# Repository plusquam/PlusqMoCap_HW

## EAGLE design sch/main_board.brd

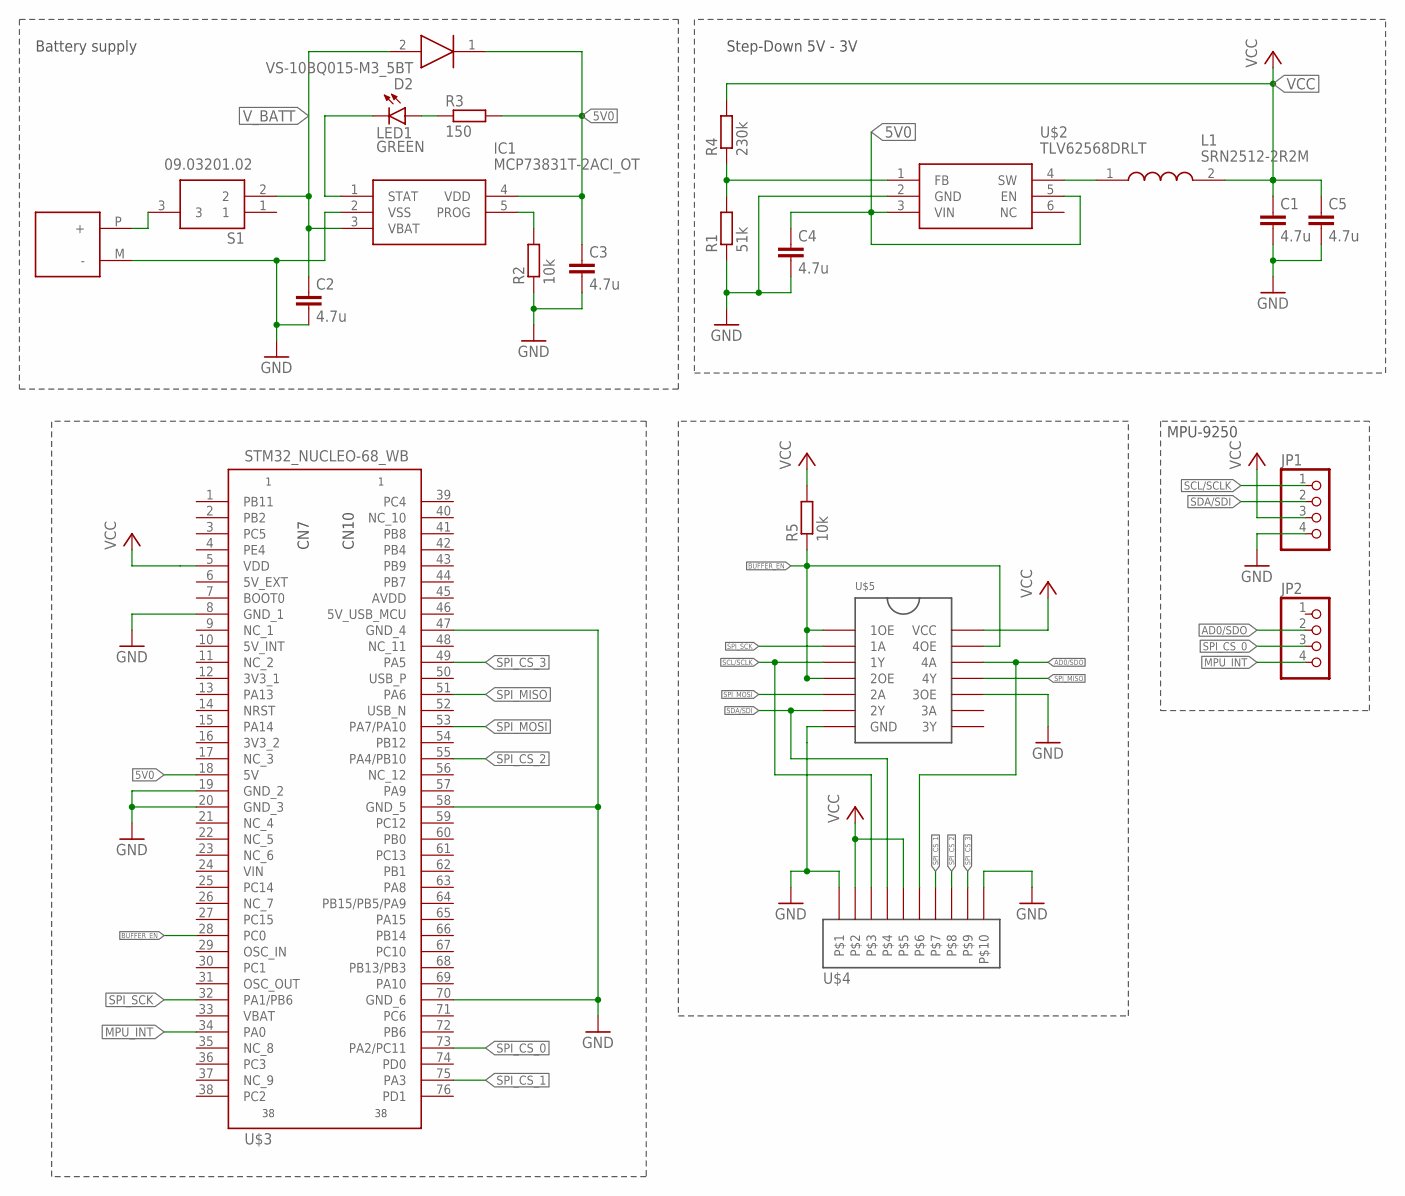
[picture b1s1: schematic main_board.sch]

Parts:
C1, C2, C3, C4, C5: 4.7u; C1206
D2: VS-10BQ015-M3_5BT; DIOM5436X244N
IC1: MCP73831T-2ACI_OT; SOT95P270X145-5N
JP1, JP2: PINHD-1X04_2.54-SMD; 1X04SMD
L1: SRN2512-2R2M; INDPM2622X120N
LED1: GREEN; CHIPLED_1206
R1: 51k; R1206
R2, R5: 10k; R1206
R3: 150; R1206
R4: 230k; R1206
S1: 09.03201.02; 090320102
U$1: BAT_FLAT_PAD; BATTERY_FLAT_PAD
U$2: TLV62568DRLT; SOT563
U$3: STM32_NUCLEO-68_WB; STM32_NUCLEO-68_FOOTPRINT
U$4: 1-2178711-2; 1-2178712-0
U$5: 74AHC126D,118; SOIC127P600X175-14N

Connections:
5V0: C3.1, C4.1, D2.1 (K), IC1.4 (VDD), R3.2, U$2.3 (VIN), U$2.5 (EN), U$3.18 (5V)
AD0/SDO: JP2.2, U$4.P$6, U$5.12 (4A)
BUFFER_EN: R5.1, U$3.28 (PC0), U$5.1 (1OE), U$5.4 (2OE), U$5.13 (4OE)
GND: C1.2, C2.2, C3.2, C4.2, C5.2, IC1.2 (VSS), JP1.4, R1.1, R2.1, U$1.M (-), U$2.2 (GND), U$3.8 (GND_1), U$3.19 (GND_2), U$3.20 (GND_3), U$3.47 (GND_4), U$3.58 (GND_5), U$3.70 (GND_6), U$4.P$1, U$4.P$10, U$5.7 (GND), U$5.10 (3OE)
MPU_INT: JP2.4, U$3.34 (PA0)
unnamed: LED1.A, R3.1
unnamed: IC1.1 (STAT), LED1.C
unnamed: IC1.5 (PROG), R2.2
unnamed: S1.3, U$1.P (+)
unnamed: L1.1, U$2.4 (SW)
unnamed: R1.2, R4.1, U$2.1 (FB)
SCL/SCLK: JP1.1, U$4.P$3, U$5.3 (1Y)
SDA/SDI: JP1.2, U$4.P$4, U$5.6 (2Y)
SPI_CS_0: JP2.3, U$3.73 (PA2/PC11)
SPI_CS_1: U$3.75 (PA3), U$4.P$7
SPI_CS_2: U$3.55 (PA4/PB10), U$4.P$8
SPI_CS_3: U$3.49 (PA5), U$4.P$9
SPI_MISO: U$3.51 (PA6), U$5.11 (4Y)
SPI_MOSI: U$3.53 (PA7/PA10), U$5.5 (2A)
SPI_SCK: U$3.32 (PA1/PB6), U$5.2 (1A)
VCC: C1.1, C5.1, JP1.3, L1.2, R4.2, R5.2, U$3.5 (VDD), U$4.P$2, U$4.P$5, U$5.14 (VCC)
V_BATT: C2.1, D2.2 (A), IC1.3 (VBAT), S1.2

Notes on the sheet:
Step-Down 5V - 3V
Battery supply
MPU-9250

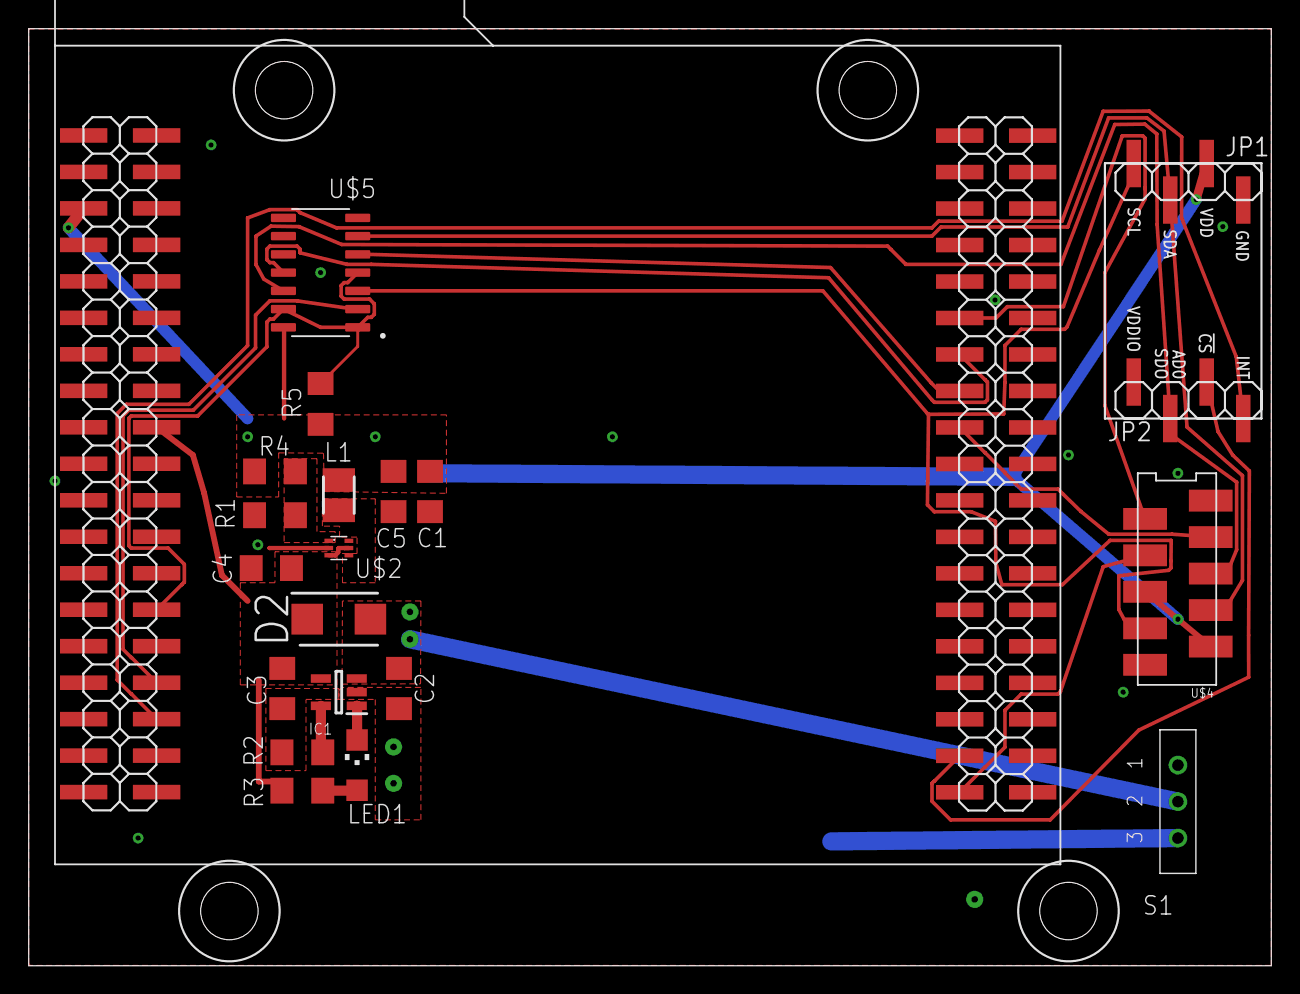
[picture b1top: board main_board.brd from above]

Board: 2 copper layers, 86.5 x 65.2 mm, 22 parts (1 on the bottom side), 22 nets.

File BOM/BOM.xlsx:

|  |  | Main Board BOM
Item # | *Ref Des | *Qty | Manufacturer | *Mfg Part # | Description / Value | *Package | Type | Your Instructions / Notes
1 | C1,C2,C3,C4,C5 | 5 | VISHAY | VJ1206V475MXQTW1BC | Ceramic Capacitor, 4.7 µF, Y5V, 10 V | C1206 | SMD | (any/open) Any cheapest and available part which match specification.
2 | D2 | 1 | Vishay | VS-10BQ015-M3/5BT | VS-10BQ015-M3/5BT Vishay SMT Schottky Diode, 15V 1A, 2-Pin DO-214AA (SMB) | DO-214AA | SMD
3 | IC1 | 1 | Microchip | MCP73831T-2ACI/OT | Li-Ion Charge Controller 4.2V SOT23-5 | SOT-23 | SMD
4 | JP1,JP2 | 2 | MULTICOMP | 2212SM-04G-75-B1-PCR | Female pin header (socket), 1x4 slots, pitch 2,54mm | 1X04SMD | SMD | Given device is only example device, it can be replaced with any cheaper and av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
5 | L1 | 1 | Bourns | SRN2512-2R2M | Bourns SRN2512 Series Shielded Wire-wound SMD Inductor with a Ferrite Core, 2.2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 | INDPM2622X120N | SMD | Given device is only example device, it can be replaced with any cheaper and av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
6 | LED1 | 1 | KINGBRIGHT | KPT-3216SGC | Green LED in 1206 package, If = 20mA, Vf = 2,2V | 1206 | SMD | Given device is only example device, it can be replaced with any cheaper and av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
7 | R1 | 1 |  |  | 100kOhm, Thick Film Chip Resistor, 1% tolerance, Max. Dissipation 250mW | R1206 | SMD | (any/open) Any cheapest and available part which match specification.
8 | R2,R5 | 2 |  |  | 10kOhm, Thick Film Chip Resistor, 1% tolerance, Max. Dissipation 250mW | R1206 | SMD | (any/open) Any cheapest and available part which match specification.
9 | R3 | 1 |  |  | 150Ohm, Thick Film Chip Resistor, 1% tolerance, Max. Dissipation 250mW | R1206 | SMD | (any/open) Any cheapest and available part which match specification.
10 | R4 | 1 |  |  | 402kOhm, Thick Film Chip Resistor, 1% tolerance, Max. Dissipation 250mW | R1206 | SMD | (any/open) Any cheapest and available part which match specification.
11 | S1 | 1 | EOZ | 09.03201.02 | 2 Way Through Hole SIP Switch SPST, 500mA, 12Vdc | 3POS | thru-hole | Given device is only example device, it can be replaced with any cheaper and av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
12 | U$2 | 1 | TEXAS INSTRUMENTS | TLV62568DRLT | DC-DC buck converter | SOT563 | SMD
13 | U$4 | 1 | AMP - TE CONNECTIVITY | 1-2178711-0 | Headers & Wire Housings FOB, SMD, 10P, Pitch: 1,27mm | 2x5POS | SMD | Given device is only example device, it can be replaced with any cheaper and av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
14 | U$5 | 1 | NEXPERIA | 74AHC126D,118 | Buffers & Line Drivers QUAD 3-STATE BUS BUF | SOIC-14 | SMD | Given device is only example device, it can be replaced with any cheaper and av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
15 | CN7,CN10 | 2 |  |  | Female pin header (socket), 2x19 (38) slots, pitch 2,54mm | 2X19SMD | SMD | (any/open) Any cheapest and available part which match specification.
 |  |  | Sensor Board BOM
Item # | *Ref Des | *Qty | Manufacturer | *Mfg Part # | Description / Value | *Package | Type | Your Instructions / Notes
1 | JP1,JP2 | 2 | MULTICOMP | 2212SM-04G-75-B1-PCR | Female pin header (socket), 1x4 slots, pitch 2,54mm | 1X04SMD | SMD | Given device is only example device, it can be replaced with any cheaper and av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
2 | U$1 | 1 | NEXPERIA | 74AHC126D,118 | Buffers & Line Drivers QUAD 3-STATE BUS BUF | SOIC-14 | SMD | Given device is only example device, it can be replaced with any cheaper and av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
3 | U$2 | 1 | AMP - TE CONNECTIVITY | 1-2178711-0 | Headers & Wire Housings FOB, SMD, 10P, Pitch: 1,27mm | 2x5POS | SMD | Given device is only example device, it can be replaced with any cheaper and av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

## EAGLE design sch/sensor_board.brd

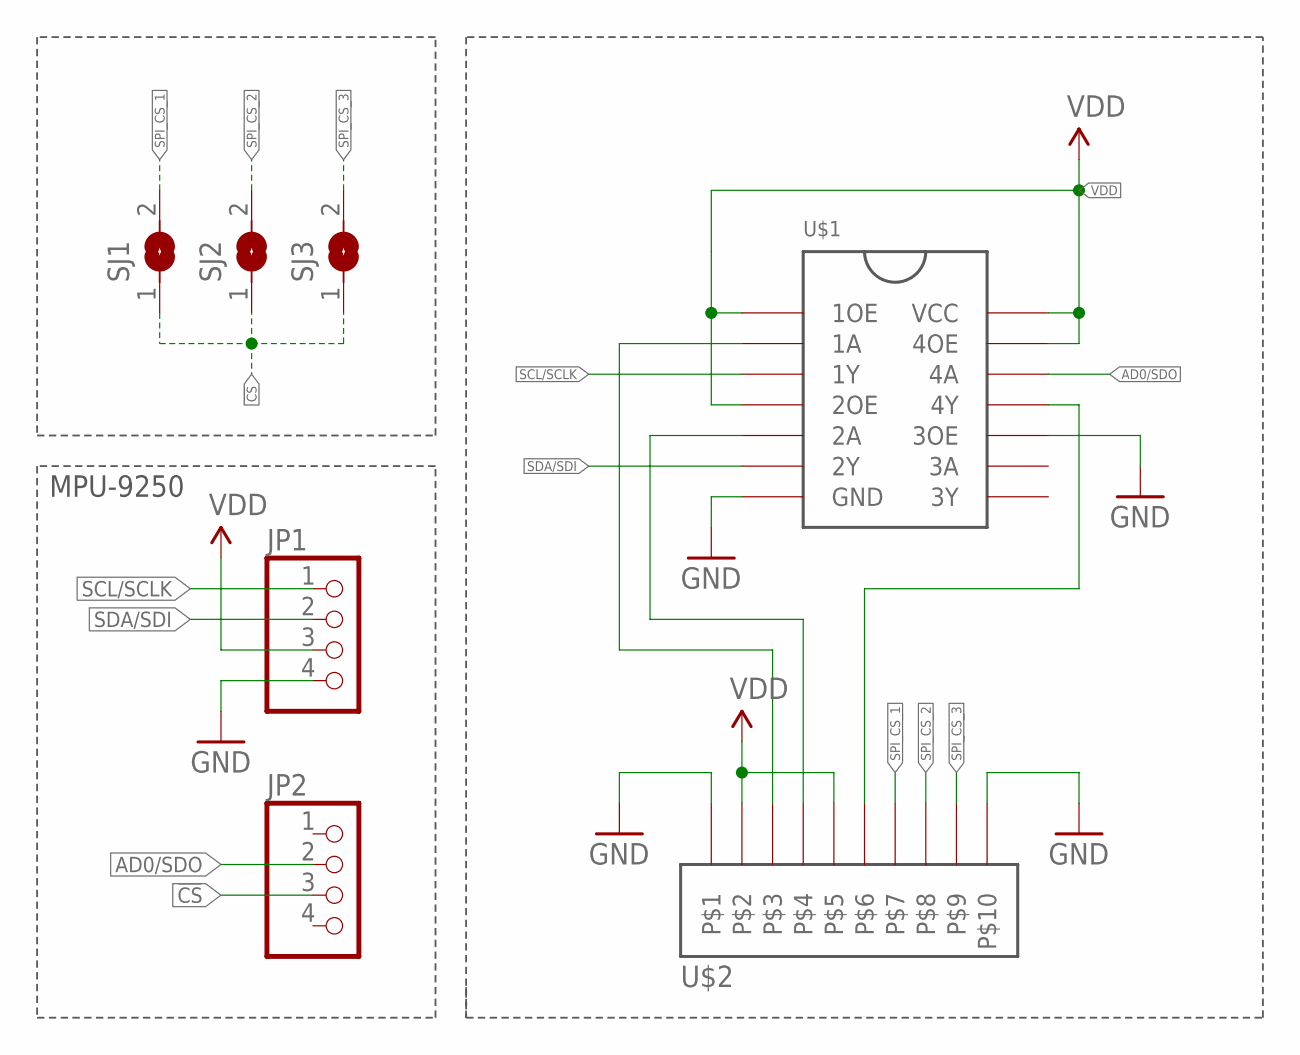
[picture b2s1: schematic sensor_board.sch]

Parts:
JP1, JP2: PINHD-1X04_2.54-SMD; 1X04SMD
SJ1, SJ2, SJ3: SJ
U$1: 74AHC126D,118; SOIC127P600X175-14N
U$2: 1-2178711-2; 1-2178712-0

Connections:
!CS: JP2.3, SJ1.1, SJ2.1, SJ3.1
AD0/SDO: JP2.2, U$1.12 (4A)
GND: JP1.4, U$1.7 (GND), U$1.10 (3OE), U$2.P$1, U$2.P$10
unnamed: U$1.2 (1A), U$2.P$3
unnamed: U$1.11 (4Y), U$2.P$6
unnamed: U$1.5 (2A), U$2.P$4
SCL/SCLK: JP1.1, U$1.3 (1Y)
SDA/SDI: JP1.2, U$1.6 (2Y)
SPI_CS_1: SJ1.2, U$2.P$7
SPI_CS_2: SJ2.2, U$2.P$8
SPI_CS_3: SJ3.2, U$2.P$9
VDD: JP1.3, U$1.1 (1OE), U$1.4 (2OE), U$1.13 (4OE), U$1.14 (VCC), U$2.P$2, U$2.P$5

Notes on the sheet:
MPU-9250

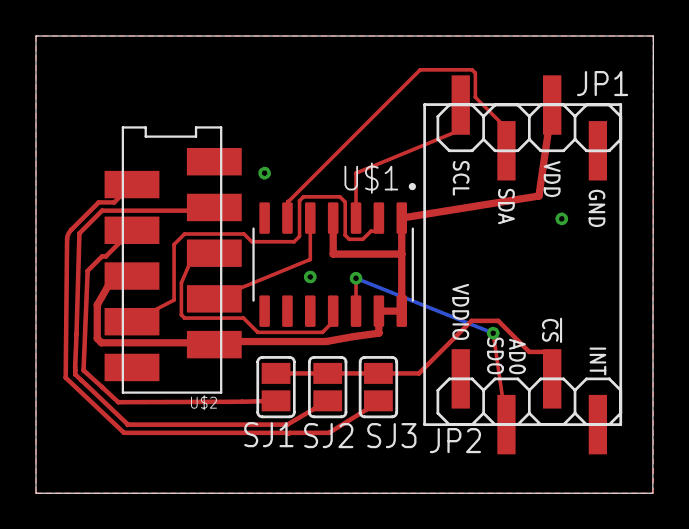
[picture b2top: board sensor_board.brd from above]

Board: 2 copper layers, 34.3 x 25.4 mm, 7 parts (0 on the bottom side), 12 nets.

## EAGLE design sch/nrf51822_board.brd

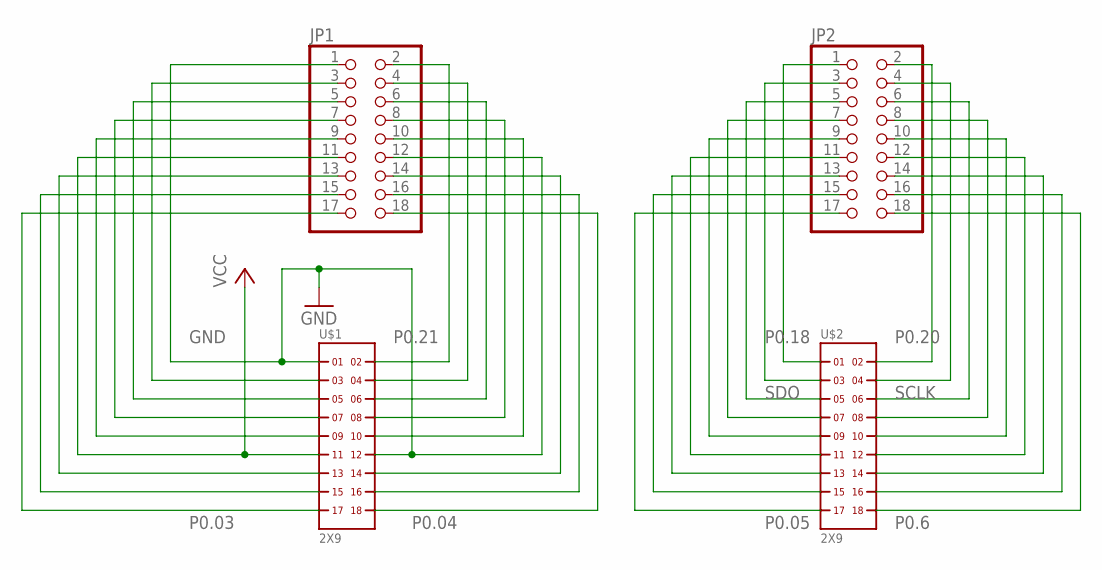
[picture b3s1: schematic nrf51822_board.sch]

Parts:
JP1, JP2: PINHD-2X9; 2X09
U$1, U$2: 2X9

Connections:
GND: JP1.1, JP1.12, U$1.1, U$1.12
unnamed: JP1.3, U$1.3
unnamed: JP1.5, U$1.5
unnamed: JP1.7, U$1.7
unnamed: JP1.9, U$1.9
unnamed: JP1.13, U$1.13
unnamed: JP1.15, U$1.15
unnamed: JP1.4, U$1.4
unnamed: JP1.6, U$1.6
unnamed: JP1.8, U$1.8
unnamed: JP1.10, U$1.10
unnamed: JP1.14, U$1.14
unnamed: JP1.16, U$1.16
unnamed: JP2.3, U$2.3
unnamed: JP2.7, U$2.7
unnamed: JP2.9, U$2.9
unnamed: JP2.11, U$2.11
unnamed: JP2.13, U$2.13
unnamed: JP2.15, U$2.15
unnamed: JP2.4, U$2.4
unnamed: JP2.8, U$2.8
unnamed: JP2.10, U$2.10
unnamed: JP2.12, U$2.12
unnamed: JP2.14, U$2.14
unnamed: JP2.16, U$2.16
P0.03: JP1.17, U$1.17
P0.04: JP1.18, U$1.18
P0.05: JP2.17, U$2.17
P0.6: JP2.18, U$2.18
P0.18: JP2.1, U$2.1
P0.20: JP2.2, U$2.2
P0.21: JP1.2, U$1.2
SCLK: JP2.6, U$2.6
SDO: JP2.5, U$2.5
VCC: JP1.11, U$1.11

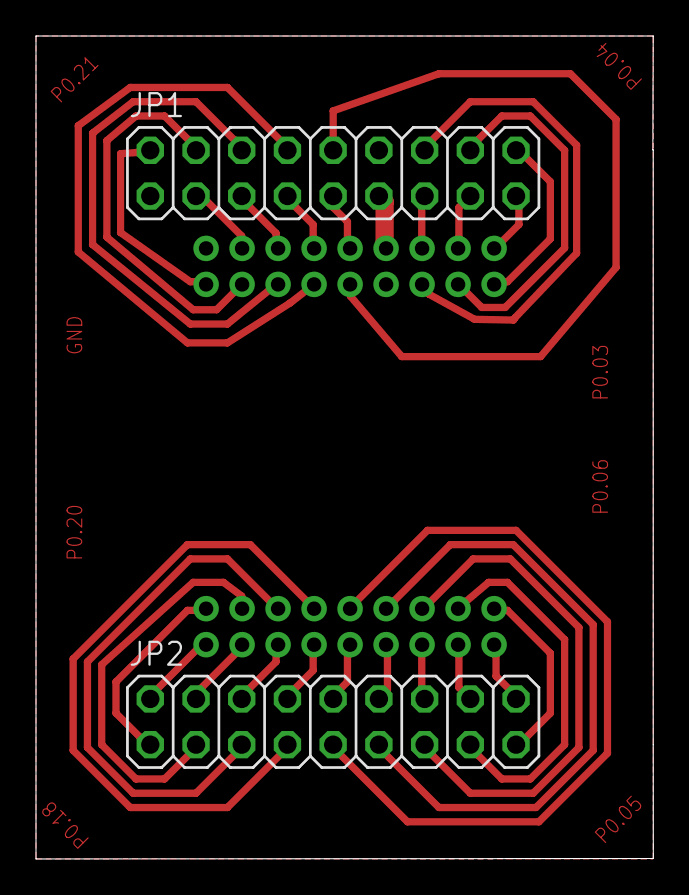
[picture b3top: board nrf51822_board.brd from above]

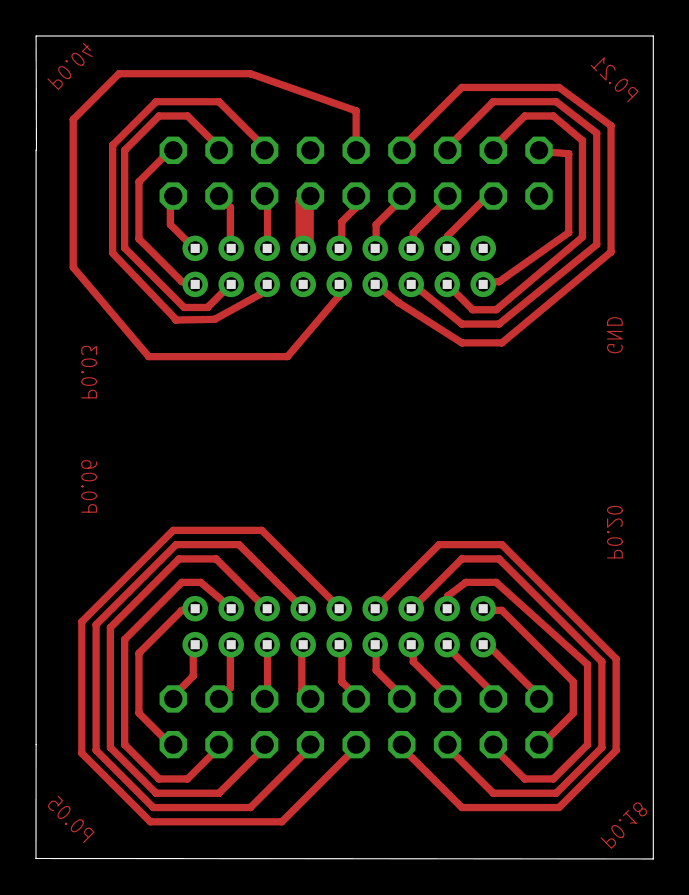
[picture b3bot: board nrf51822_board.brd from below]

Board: 2 copper layers, 34.3 x 45.7 mm, 4 parts (2 on the bottom side), 35 nets.

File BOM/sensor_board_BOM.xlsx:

|  |  | Sensor Board BOM
Item # | *Ref Des | *Qty | Manufacturer | *Mfg Part # | Description / Value | *Package | Type | Your Instructions / Notes
1 | JP1,JP2 | 2 | MULTICOMP | 2212SM-04G-75-B1-PCR | Female pin header (socket), 1x4 slots, pitch 2,54mm | 1X04SMD | SMD | Given device is only example device, it can be replaced with any cheaper and av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
2 | U$1 | 1 | NEXPERIA | 74AHC126D,118 | Buffers & Line Drivers QUAD 3-STATE BUS BUF | SOIC-14 | SMD | Given device is only example device, it can be replaced with any cheaper and av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
3 | U$2 | 1 | AMP - TE CONNECTIVITY | 1-2178711-0 | Headers & Wire Housings FOB, SMD, 10P, Pitch: 1,27mm | 2x5POS | SMD | Given device is only example device, it can be replaced with any cheaper and av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

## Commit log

2019-05-17 Import source files from PlusqMoCap repo.
2019-07-07 Remove obsolete license file.
2019-07-08 Add docs for STM32WB, Remove unused power supply elements.
2019-07-09 Add library for STM32WB prototype board.
2019-07-09 Create LICENSE
2019-08-14 Add STM32WB board part, add sensor connector part
2019-08-16 Main board ver. 1.0
2019-08-21 Ready for production HW version
2019-09-13 Add BOM files
2019-09-13 Change feedback resistors for DC/DC converter
2019-09-15 Update schematic documentation
2019-09-26 Add cases design and CAM files

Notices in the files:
parts and their libraries:
SparkFun-Aesthetics: Licensing: Creative Commons ShareAlike 4.0 International - https://creativecommons.org/licenses/by-sa/4.0
